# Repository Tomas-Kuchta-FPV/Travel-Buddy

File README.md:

# Travel-Buddy
Pocketable, smart and sleek Meshtastic node. With keyboard, Eink screen, GPS and all day baterry life thanks to it's Solar panel. Based on the [Seed Studio Wio tracker L1](https://meshtastic.org/docs/hardware/devices/seeed-studio/wio-series/tracker-l1/).  

Took inspiration from the original idea of Meshtastic and made a hiker, prepper and EDC friendly device.  

## Specifications
- **Wio tracker L1 Eink** a nifty main board
    - **GPS** to know where you and your frinds are
    - **nRF52840** to sip power bit by bit
    - **2.3 Inch Eink screen** so you never miss anything 
    - **Navigation buttons** for easy and intuitive control
    - **On-Off button** to save power for when the Sun is hiding
    - **Antenna** the default antenna is pretty good
- [3x4 Nokia style](https://en.wikipedia.org/wiki/T9_%28predictive_text%29) keyboard for easy texting
- **Solar panel** so your battery can be rechargerd from 0 to 100 in just two daays
- Space for a **big battery** for the days when the sun isn't shining

| Front                       | Back                      |
| --------------------------- | ------------------------- |
|  |  |

## Use cases
Built for hikers, makers, preppers, and everyday carry adventurers who like their tech smart, tough, and a little bit magical.

**Hikers** can wander freely without worrying about battery life, coverage, or fragile screens. Solar charging keeps it alive on long trails, GPS keeps you oriented, and Meshtastic keeps you connected with your group even when civilization politely vanishes. The only real responsibility is remembering to bring it along. 😅

**Makers** will feel right at home. It’s open-source, hackable, and begging to be customized. New firmware ideas, experimental features, clever power optimizations. This thing is a playground for curious minds who like to bend hardware to their will.

**Preppers** get a resilient, low-power communication tool that keeps working when the grid doesn’t. Solar charging, long battery life, offline mesh networking, and the ability to tinker and repair make it a quiet little survival ally that doesn’t ask for much.

**EDC** enthusiasts get a pocketable device that just works. No constant charging anxiety, no fragile glass screens, no babysitting. Toss it in your bag or clip it to your gear and let it quietly do its job, day after day, powered by sunlight and good engineering dreams.

| Top                     | Front                                             | PCB                               |
| ----------------------- | ------------------------------------------------- | --------------------------------- |
|  |  |  |

## My motivation to build it
It is some sort of challange to see wether I can do a project thar can be comercialized, almost evhery project can end up making some money but many times it depends wether its worth it.  
I have way more faith when I built the physical prototype as it seems like a super cool and handy idea.  
And also it's a whole lot of fun to do a project that doesn't need to worry about money or the general public. ;)

## BOM
[BOM.ods](/BOM.ods)

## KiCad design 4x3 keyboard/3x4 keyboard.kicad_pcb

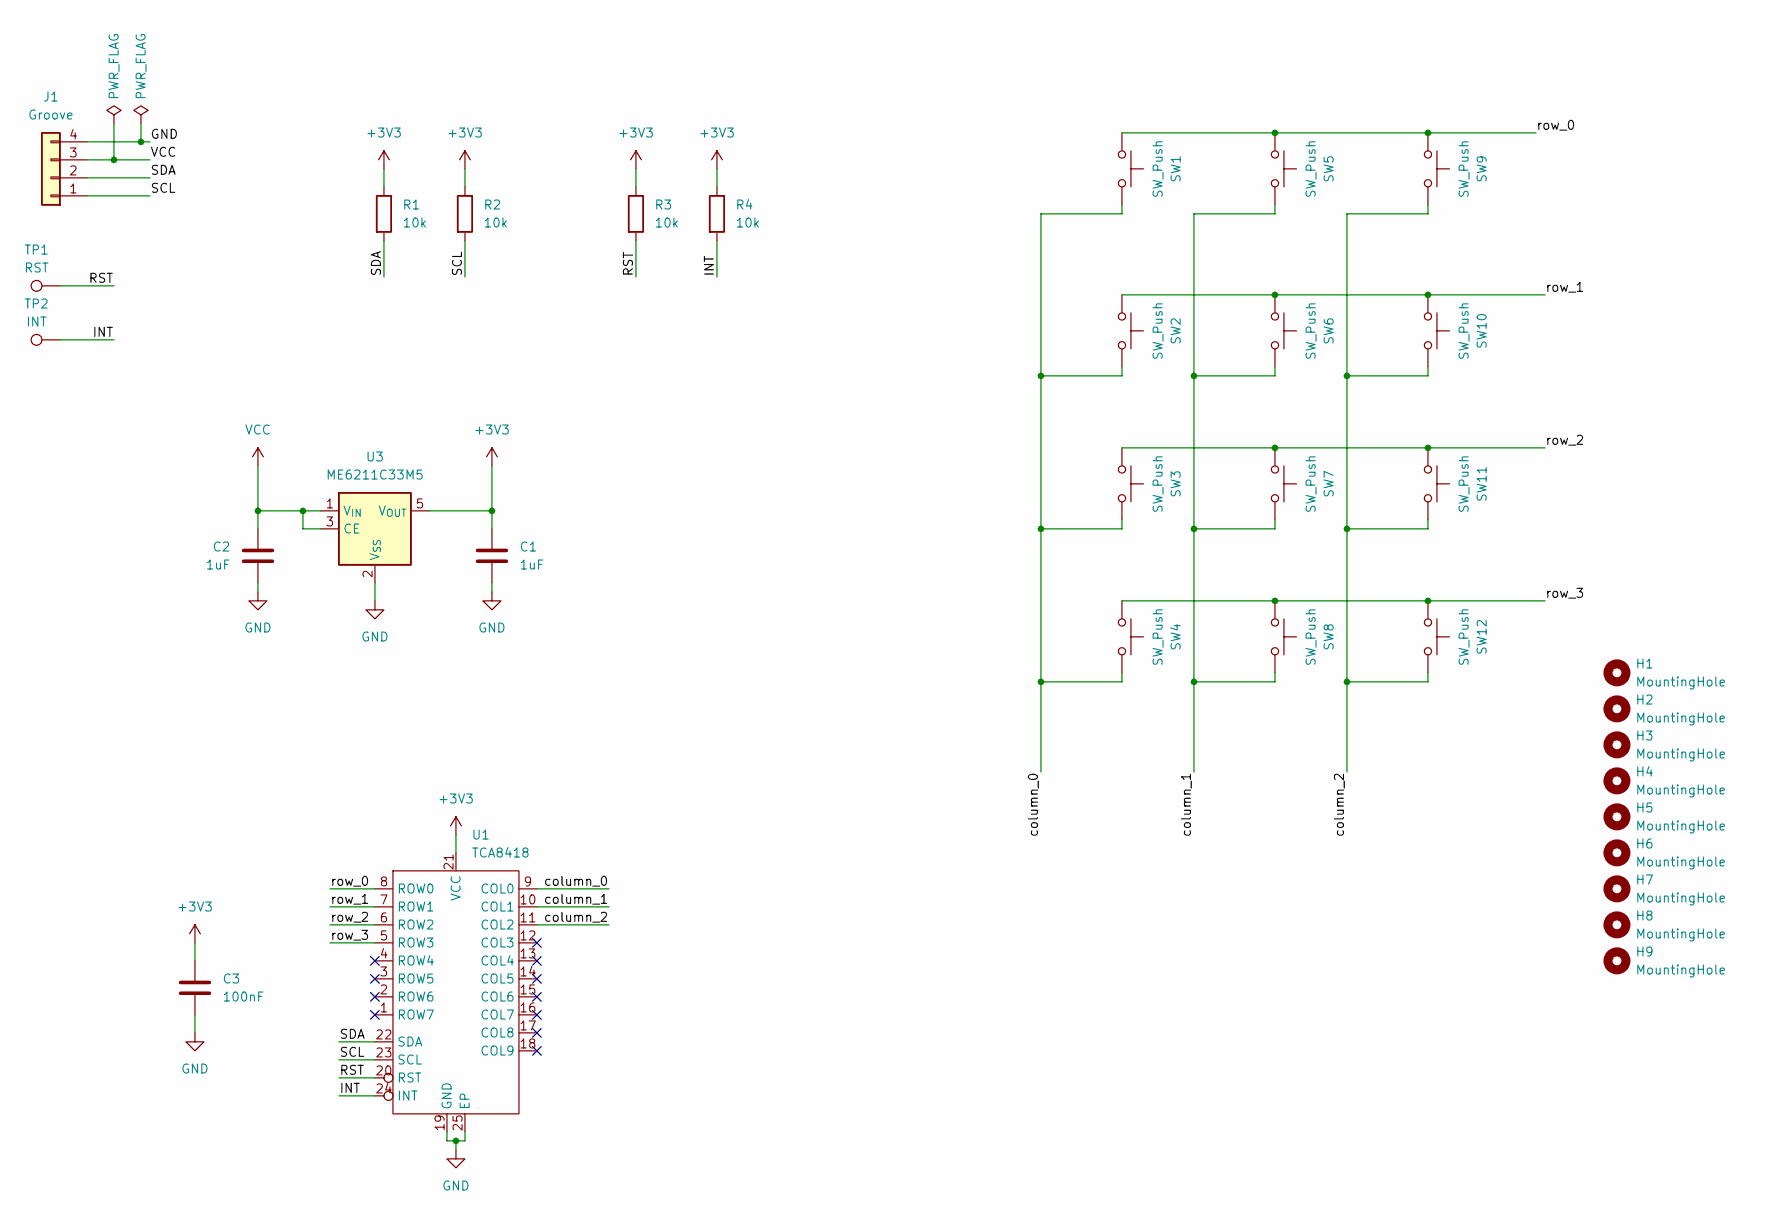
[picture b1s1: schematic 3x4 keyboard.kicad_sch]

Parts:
C1, C2: 1uF; C_0805_2012Metric_Pad1.18x1.45mm_HandSolder; LCSC C28323
C3: 100nF; C_0805_2012Metric_Pad1.18x1.45mm_HandSolder; LCSC C49678
H1, H2, H3, H4, H5, H6, H7, H8, H9: MountingHole; MountingHole_2.1mm
J1: Groove; JST_PH_S4B-PH-K_1x04_P2.00mm_Horizontal; LCSC C157926
R1, R2, R3, R4: 10k; R_0805_2012Metric_Pad1.20x1.40mm_HandSolder; LCSC 0805
SW1, SW2, SW3, SW4, SW5, SW6, SW7, SW8, SW9, SW10, SW11, SW12: SW_Push; SW_Push_1P1T_XKB_TS-1187A; LCSC C318884
TP1: RST; TestPoint_Pad_2.0x2.0mm
TP2: INT; TestPoint_Pad_2.0x2.0mm
U1: TCA8418; WQFN-24-1EP_4x4mm_P0.5mm_EP2.45x2.45mm; LCSC C138713
U3: ME6211C33M5; SOT-23-5; LCSC C82942

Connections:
+3V3: C1.1, C3.1, R1.1, R2.1, R3.1, R4.1, U1.21 (VCC), U3.5 (V_{OUT})
/INT: R4.2, TP2.1, U1.24 (INT)
/RST: R3.2, TP1.1, U1.20 (RST)
/SCL: J1.1, R2.2, U1.23 (SCL)
/SDA: J1.2, R1.2, U1.22 (SDA)
/column_0: SW1.2, SW2.2, SW3.2, SW4.2, U1.9 (COL0)
/column_1: SW5.2, SW6.2, SW7.2, SW8.2, U1.10 (COL1)
/column_2: SW9.2, SW10.2, SW11.2, SW12.2, U1.11 (COL2)
/row_0: SW1.1, SW5.1, SW9.1, U1.8 (ROW0)
/row_1: SW2.1, SW6.1, SW10.1, U1.7 (ROW1)
/row_2: SW3.1, SW7.1, SW11.1, U1.6 (ROW2)
/row_3: SW4.1, SW8.1, SW12.1, U1.5 (ROW3)
GND: C1.2, C2.2, C3.2, J1.4, U1.19 (GND), U1.25 (EP), U3.2 (V_{SS})
VCC: C2.1, J1.3, U3.1 (V_{IN}), U3.3 (CE)

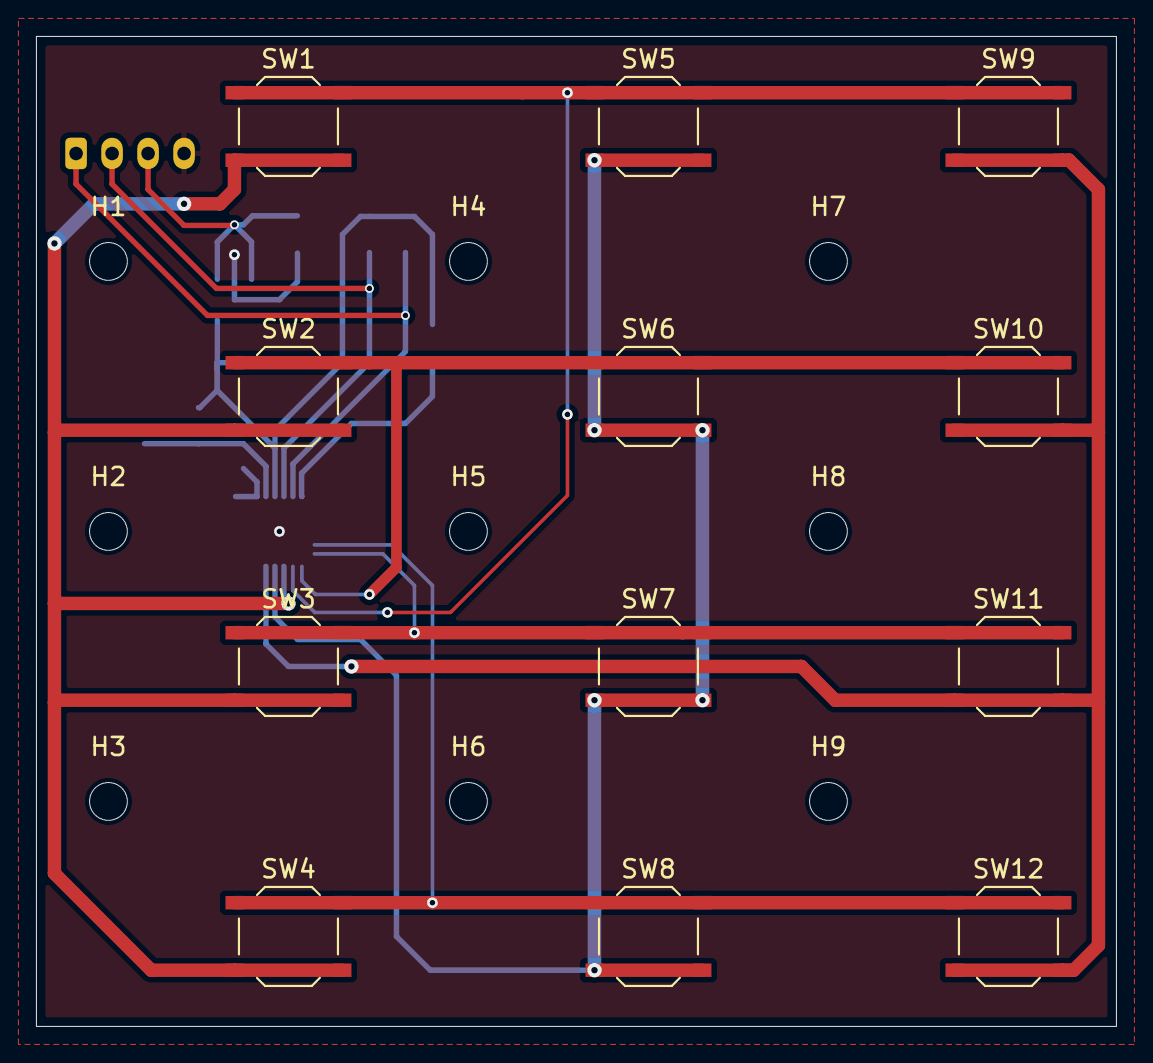
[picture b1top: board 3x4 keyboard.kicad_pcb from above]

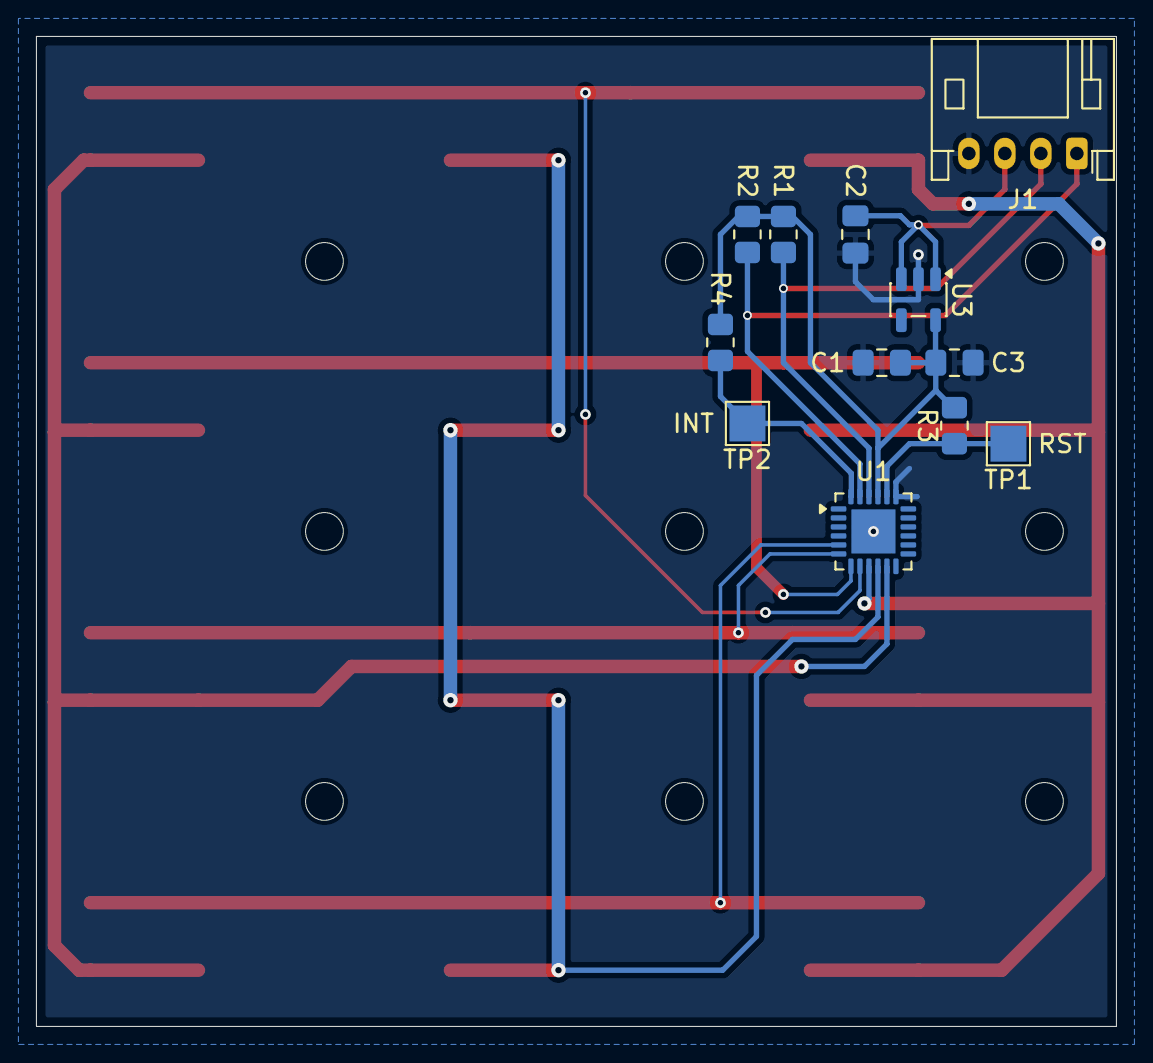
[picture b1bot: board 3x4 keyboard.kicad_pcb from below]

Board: 2 copper layers, 60.0 x 55.0 mm, 33 parts (12 on the bottom side), 14 nets.

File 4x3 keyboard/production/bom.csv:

Designator,Footprint,Quantity,Value,LCSC Part #
"C1, C2",0805,2,1uF,C28323
C3,0805,1,100nF,C49678
J1,JST_PH_S4B-PH-K_1x04_P2.00mm_Horizontal,1,Groove,C157926
"R1, R2, R3, R4",0805,4,10k,0805
"SW1, SW10, SW11, SW12, SW2, SW3, SW4, SW5, SW6, SW7, SW8, SW9",SW_Push_1P1T_XKB_TS-1187A,12,SW_Push,C318884
TP1,TestPoint_Pad_2.0x2.0mm,1,RST,
TP2,TestPoint_Pad_2.0x2.0mm,1,INT,
U1,WQFN-24-1EP_4x4mm_P0.5mm_EP2.45x2.45mm,1,TCA8418,C138713
U3,SOT-23-5,1,ME6211C33M5,C82942

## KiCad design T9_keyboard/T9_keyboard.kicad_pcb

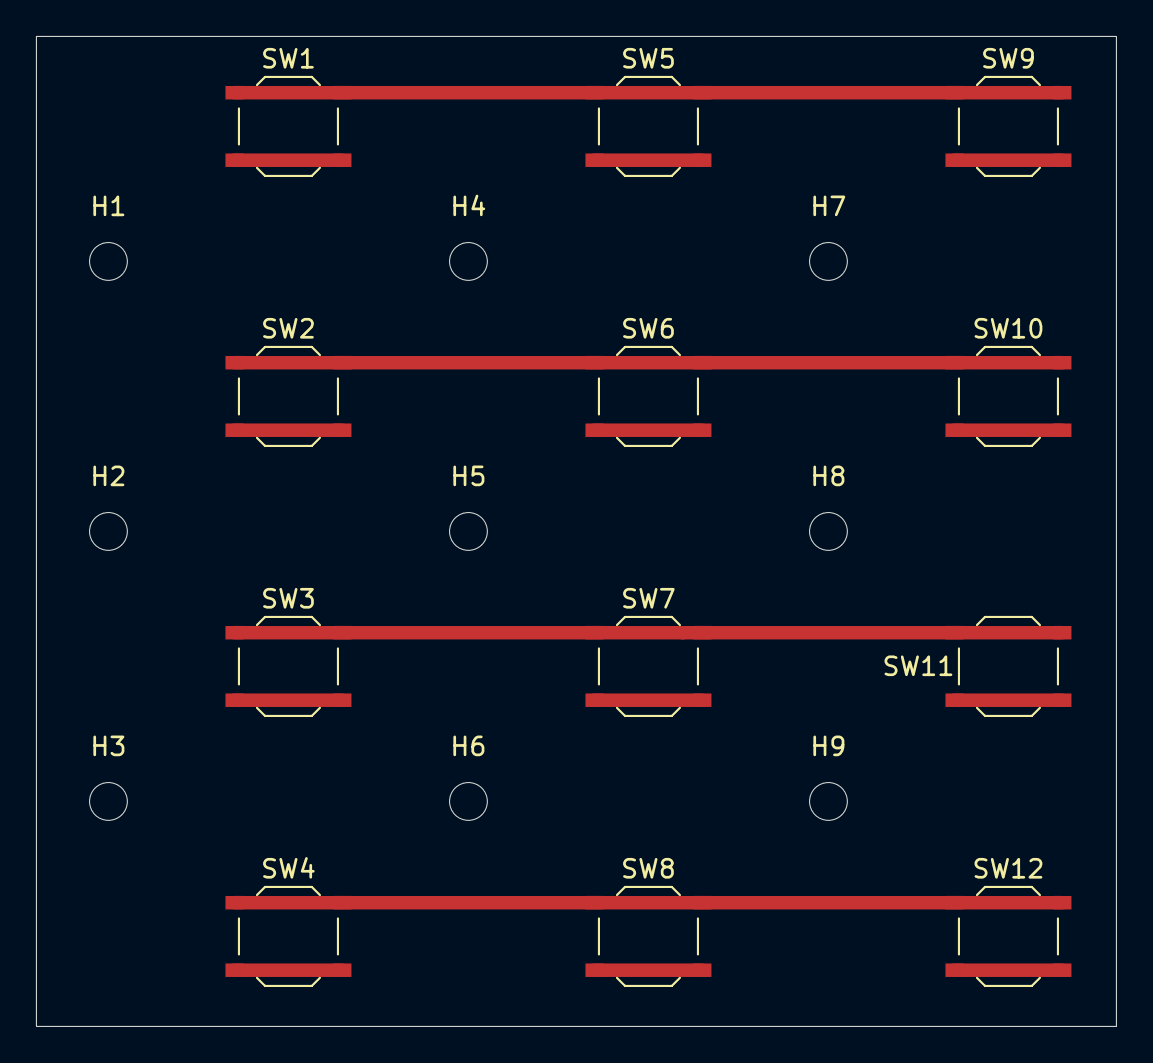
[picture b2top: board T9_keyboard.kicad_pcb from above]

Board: 2 copper layers, 60.0 x 55.0 mm, 21 parts (0 on the bottom side), 4 nets.

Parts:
H1, H2, H3, H4, H5, H6, H7, H8, H9: MountingHole; MountingHole_2.1mm
SW1, SW2, SW3, SW4, SW5, SW6, SW7, SW8, SW9, SW10, SW11, SW12: SW_Push; SW_Push_1P1T_XKB_TS-1187A

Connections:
/row_0: SW1.1, SW5.1, SW9.1
/row_1: SW2.1, SW6.1, SW10.1
/row_2: SW3.1, SW7.1, SW11.1
/row_3: SW4.1, SW8.1, SW12.1

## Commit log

2025-09-03 Added the project.
2025-09-03 made readme
2026-01-21 Finished the schematic
2026-01-22 Finishing touches and a readme
2026-01-22 smoL fix
2026-01-24 Finish line!
2026-02-13 update step files
2026-03-07 Updated BOM for newer links and deduplicated BOMs.
2026-03-16 updated 3d prints
2026-03-28 finished the first prototype
2026-03-28 fixed readme
2026-03-29 created a draft of a school presentation on this project
2026-03-31 added a prezentation for SOC day at our school
2026-04-22 almost finisjed with the next wersion
2026-05-01 added labels!!
